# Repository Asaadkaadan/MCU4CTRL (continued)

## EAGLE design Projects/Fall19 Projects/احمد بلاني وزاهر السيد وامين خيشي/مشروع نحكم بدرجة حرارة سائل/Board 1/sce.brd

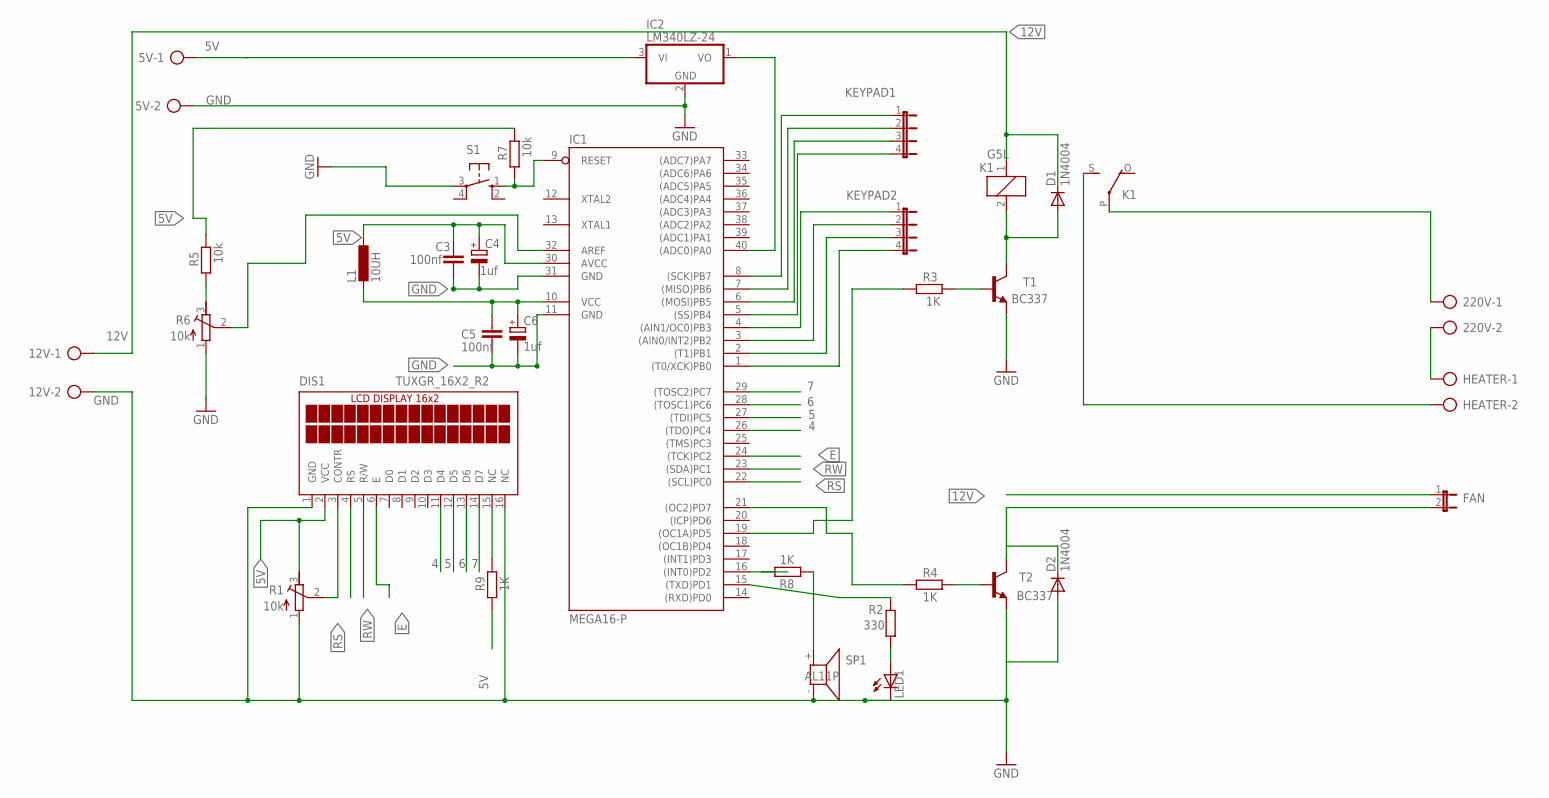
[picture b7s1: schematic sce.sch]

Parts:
5V, 12V, 220V: AK500/2
C3, C5: 100nf; C025-025X050
C4, C6: 1uf; E2,5-5
D1, D2: 1N4004; DO41-10
DIS1: TUXGR_16X2_R2
FAN: JP1E; JP1
HEATER: AK500/2
IC1: MEGA16-P; DIL40
IC2: LM340LZ-24; TO92
K1: G5L; G5LE
KEYPAD1, KEYPAD2: JP4E; JP4
L1: 10UH; 6000-XXXX-RC
LED1: LED5MM
R1, R6: 10k; RTRIM3339P
R2: 330; 0207/10
R3, R4, R8, R9: 1K; 0207/10
R5, R7: 10k; 0207/10
S1: 10-XX; B3F-10XX
SP1: AL11P
T1, T2: BC337; TO92

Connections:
1: C5.1, C6.+, IC1.10 (VCC), L1.2
4: DIS1.11 (D4), IC1.26 ((TDO)PC4)
5: DIS1.12 (D5), IC1.27 ((TDI)PC5)
5V: 5V.1, C3.1, C4.+, DIS1.2 (VCC), IC1.30 (AVCC), IC2.3 (VI), L1.1, R1.3 (E), R5.2, R7.2, R9.1
6: DIS1.13 (D6), IC1.28 ((TOSC1)PC6)
7: DIS1.14 (D7), IC1.29 ((TOSC2)PC7)
12V: 12V.1, D1.C, FAN.1, K1.1
E: DIS1.6 (E), IC1.24 ((TCK)PC2)
GND: 5V.2, 12V.2, C3.2, C4.-, C5.2, C6.-, D2.A, DIS1.1 (GND), DIS1.16 (NC), IC1.11 (GND), IC1.31 (GND), IC2.2 (GND), LED1.K (C), R1.1 (A), R6.1 (A), SP1.- (1), T1.1 (E), T2.1 (E)
HOT: IC1.40 ((ADC0)PA0), IC2.1 (VO)
KEYPAD2: IC1.1 ((T0/XCK)PB0), KEYPAD2.4
unnamed: IC1.9 (RESET), R7.1, S1.1 (S)
unnamed: R4.2, T2.2 (B)
unnamed: R3.2, T1.2 (B)
unnamed: IC1.21 ((OC2)PD7), R4.1
unnamed: IC1.3 ((AIN0/INT2)PB2), KEYPAD2.2
unnamed: IC1.19 ((OC1A)PD5), R3.1
unnamed: D1.A, K1.2, T1.3 (C)
unnamed: IC1.5 ((SS)PB4), KEYPAD1.4
unnamed: 220V.1, K1.P
unnamed: 220V.2, HEATER.1
unnamed: IC1.16 ((INT0)PD2), R8.2
unnamed: IC1.2 ((T1)PB1), KEYPAD2.3
unnamed: HEATER.2, K1.S
unnamed: IC1.4 ((AIN1/OC0)PB3), KEYPAD2.1
unnamed: D2.C, FAN.2, T2.3 (C)
unnamed: IC1.15 ((TXD)PD1), R2.2
unnamed: DIS1.3 (CONTR), R1.2 (S)
unnamed: IC1.6 ((MOSI)PB5), KEYPAD1.3
unnamed: LED1.A, R2.1
unnamed: IC1.7 ((MISO)PB6), KEYPAD1.2
unnamed: R8.1, SP1.+ (2)
unnamed: IC1.8 ((SCK)PB7), KEYPAD1.1
unnamed: IC1.32 (AREF), R6.2 (S)
unnamed: R5.1, R6.3 (E)
unnamed: DIS1.15 (NC), R9.2
RS: DIS1.4 (RS), IC1.22 ((SCL)PC0)
RW: DIS1.5 (R/W), IC1.23 ((SDA)PC1)

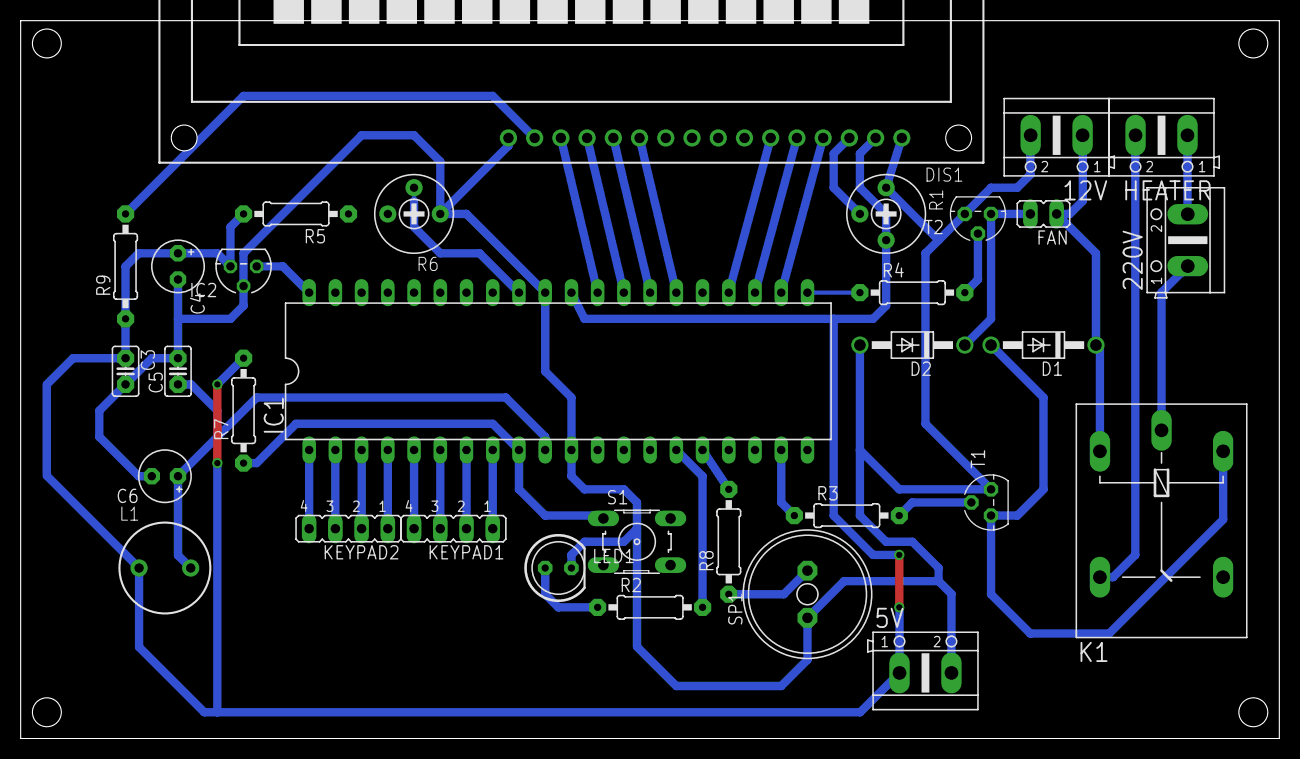
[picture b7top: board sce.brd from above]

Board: 2 copper layers, 121.9 x 69.5 mm, 32 parts (0 on the bottom side), 38 nets.

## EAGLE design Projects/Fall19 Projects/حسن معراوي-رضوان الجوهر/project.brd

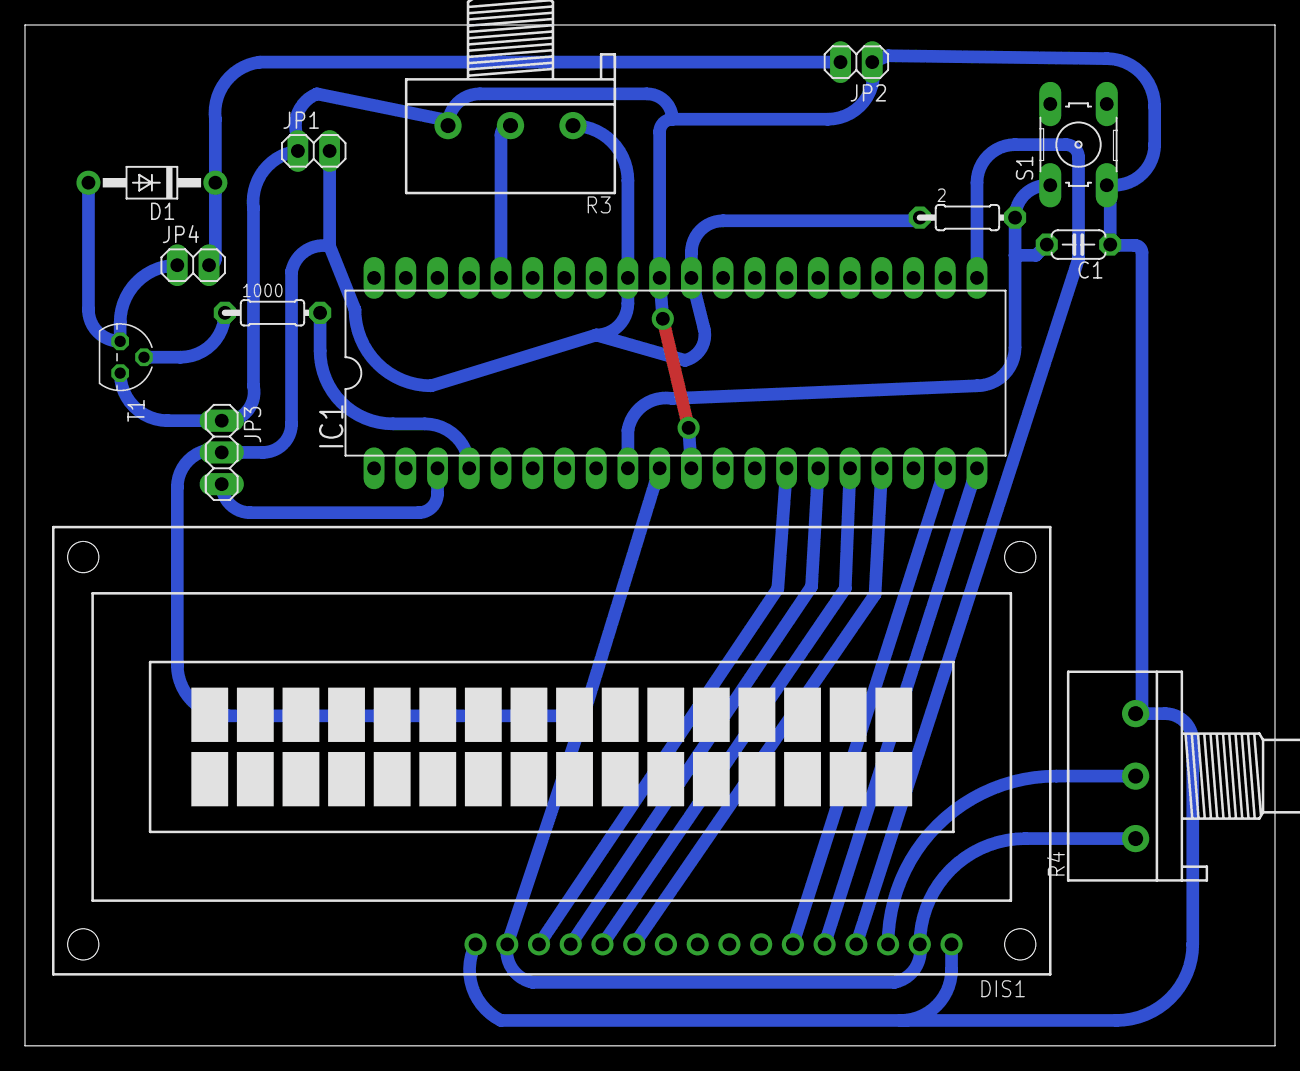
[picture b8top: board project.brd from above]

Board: 2 copper layers, 100.1 x 81.7 mm, 14 parts (0 on the bottom side), 17 nets.

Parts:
2, 1000: 0204/7
C1: C050-024X044
D1: 1N4004; DO41-10
DIS1: TUXGR_16X2_R2
IC1: MEGA16-P; DIL40
JP1, JP2, JP4: 1X02
JP3: 1X03
R3, R4: 3RP/1610N
S1: B3F-10XX
T1: BC337; TO92

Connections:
12V: D1.C, JP2.2, JP4.2
GND: C1.1, DIS1.1, DIS1.16, IC1.11, IC1.31, JP1.1, JP2.1, JP3.1, R3.3, R4.3, S1.3, T1.1
unnamed: IC1.36, R3.2
unnamed: IC1.3, JP3.3
unnamed: DIS1.4, IC1.21
unnamed: 2.2, C1.2, IC1.9, S1.1
unnamed: DIS1.5, IC1.20
unnamed: D1.A, JP4.1, T1.3
unnamed: 1000.1, T1.2
unnamed: 1000.2, IC1.4
unnamed: DIS1.6, IC1.19
unnamed: DIS1.11, IC1.17
unnamed: DIS1.12, IC1.16
unnamed: DIS1.13, IC1.15
unnamed: DIS1.14, IC1.14
unnamed: DIS1.3, R4.2
VCC: 2.1, DIS1.2, DIS1.15, IC1.10, IC1.30, IC1.32, JP1.2, JP3.2, R3.1, R4.1
